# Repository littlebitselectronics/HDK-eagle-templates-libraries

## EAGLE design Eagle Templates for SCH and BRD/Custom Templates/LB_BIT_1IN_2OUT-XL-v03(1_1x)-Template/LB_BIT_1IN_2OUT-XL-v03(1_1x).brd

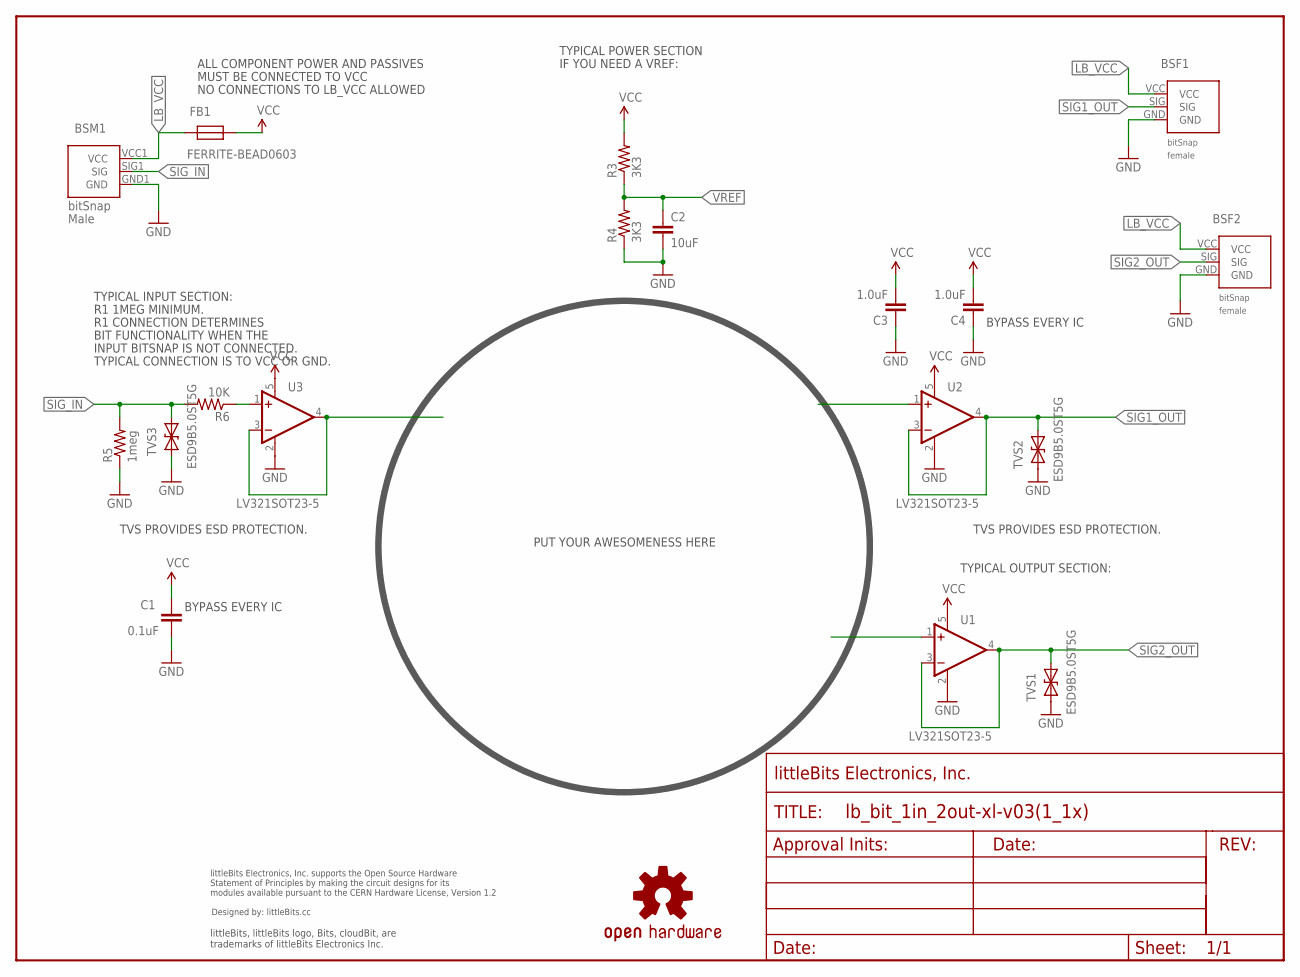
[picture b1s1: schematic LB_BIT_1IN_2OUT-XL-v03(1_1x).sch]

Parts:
BSF1, BSF2: BITSNAP_V03_FEMALE
BSM1: BITSNAP_V03_MALE
C1: 0.1uF; CAP-0603
C2: 10uF; CAP-0603
C3, C4: 1.0uF; CAP-0603
FB1: FERRITE-BEAD0603; R0603
FRAME1: FRAME-LETTER; FABDWG01-OHW
R3, R4: 3K3; RES-0603
R5: 1meg; RES-0603
R6: 10K; RES-0603
TVS1, TVS2, TVS3: ESD9B5.0ST5G; SOD-923
U1, U2, U3: LV321SOT23-5; SOT23-5
U$1: OSHW-LOGOL; OSHW-LOGO-L
U$2: OSHWCREDIT

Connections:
GND: BSF1.GND, BSF2.GND, BSM1.GND1 (GND), C1.2, C2.2, C3.1, C4.1, R4.1, R5.1, TVS1.1 (A), TVS2.1 (A), TVS3.1 (A), U1.2 (V-), U2.2 (V-), U3.2 (V-)
LB_VCC: BSF1.VCC, BSF2.VCC, BSM1.VCC1 (VCC), FB1.2
unnamed: U3.3 (-IN), U3.4 (OUT)
unnamed: R6.1, U3.1 (+IN)
SIG1_OUT: BSF1.SIG, TVS2.2 (C), U2.3 (-IN), U2.4 (OUT)
SIG2_OUT: BSF2.SIG, TVS1.2 (C), U1.3 (-IN), U1.4 (OUT)
SIG_IN: BSM1.SIG1 (SIG), R5.2, R6.2, TVS3.2 (C)
VCC: C1.1, C3.2, C4.2, FB1.1, R3.2, U1.5 (V+), U2.5 (V+), U3.5 (V+)
VREF: C2.1, R3.1, R4.2

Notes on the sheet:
R1 1MEG MINIMUM.
R1 CONNECTION DETERMINES
BIT FUNCTIONALITY WHEN THE
INPUT BITSNAP IS NOT CONNECTED.
TYPICAL CONNECTION IS TO VCC OR GND.
TVS PROVIDES ESD PROTECTION.
TYPICAL INPUT SECTION:
TYPICAL POWER SECTION
IF YOU NEED A VREF:
PUT YOUR AWESOMENESS HERE
BYPASS EVERY IC
TYPICAL OUTPUT SECTION:
NO CONNECTIONS TO LB_VCC ALLOWED
ALL COMPONENT POWER AND PASSIVES
MUST BE CONNECTED TO VCC

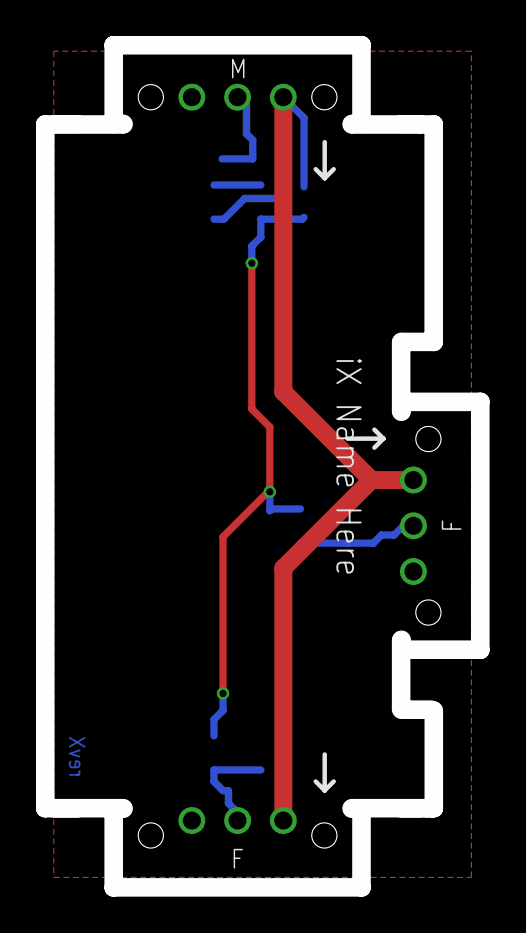
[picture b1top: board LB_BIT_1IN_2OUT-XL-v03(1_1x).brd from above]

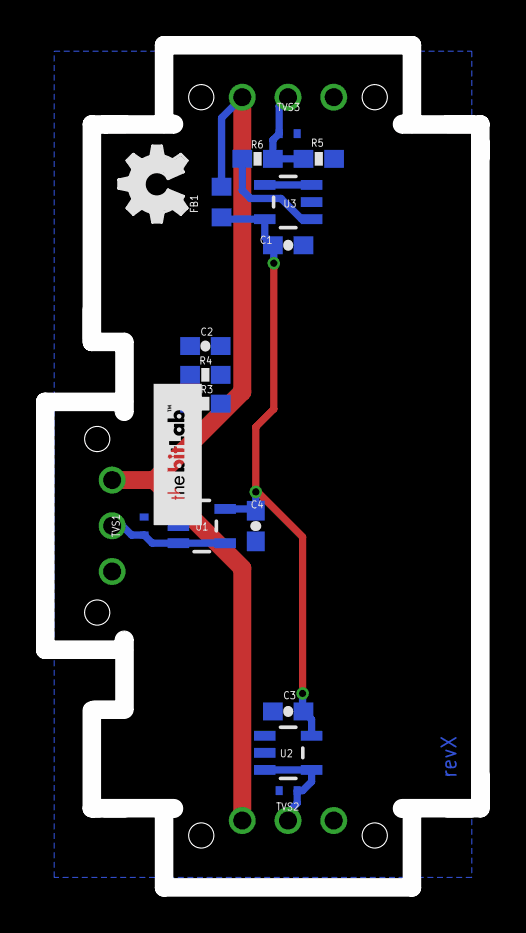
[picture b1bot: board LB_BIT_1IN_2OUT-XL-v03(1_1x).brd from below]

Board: 2 copper layers, 23.2 x 45.8 mm, 23 parts (15 on the bottom side), 9 nets.

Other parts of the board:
U$3: BITLAB-LOGO
U$8: OSHW_FILLX150_NOTEXT

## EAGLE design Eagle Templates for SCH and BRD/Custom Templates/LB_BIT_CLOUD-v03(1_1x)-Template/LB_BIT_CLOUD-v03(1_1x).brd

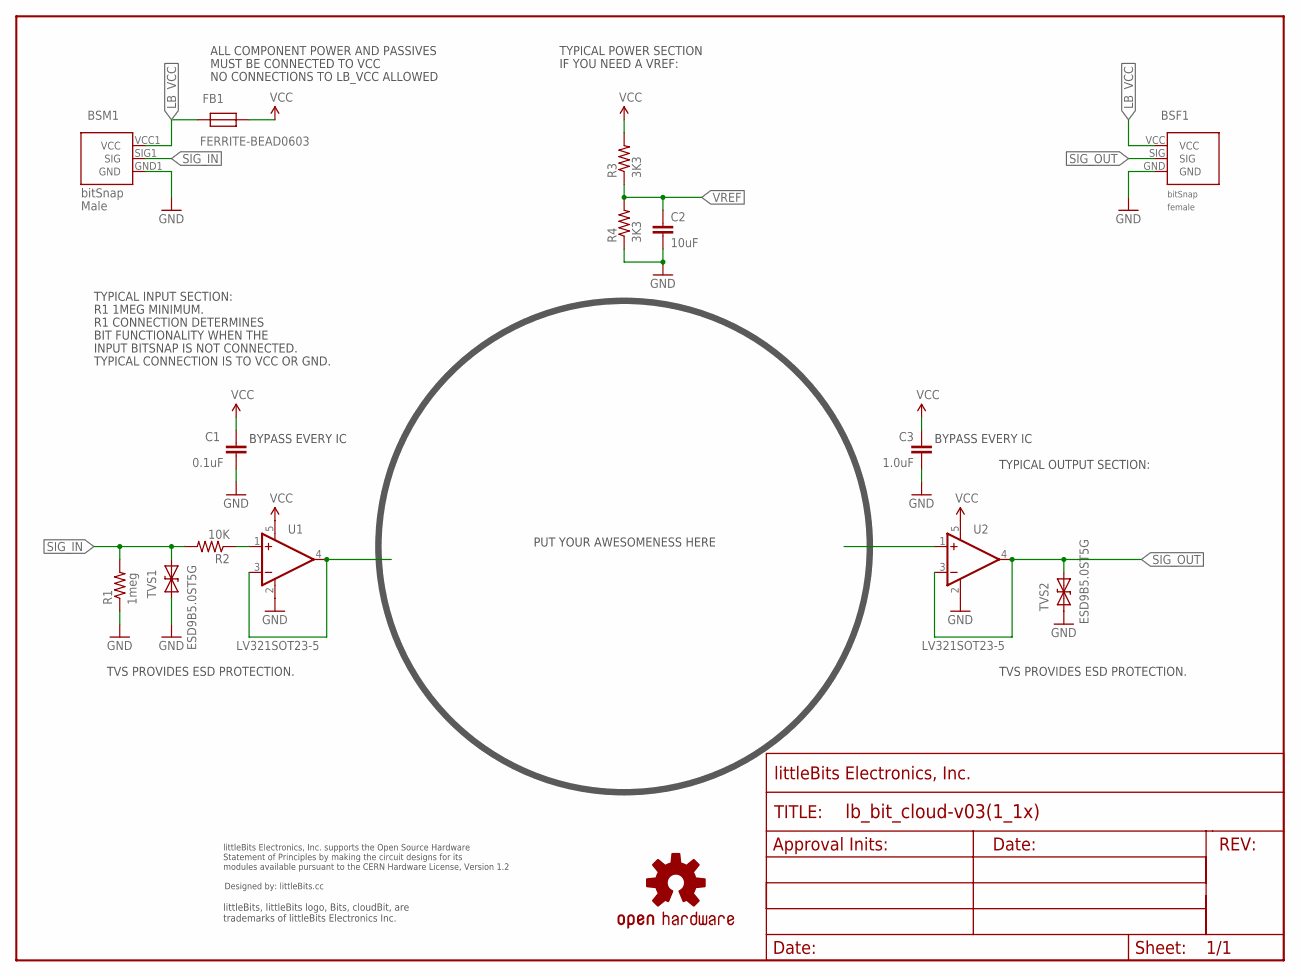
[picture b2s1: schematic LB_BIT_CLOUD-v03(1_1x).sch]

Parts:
BSF1: BITSNAP_V03_FEMALE
BSM1: BITSNAP_V03_MALE
C1: 0.1uF; CAP-0603
C2: 10uF; CAP-0603
C3: 1.0uF; CAP-0603
FB1: FERRITE-BEAD0603; R0603
FRAME1: FRAME-LETTER; FABDWG01-OHW
R1: 1meg; RES-0603
R2: 10K; RES-0603
R3, R4: 3K3; RES-0603
TVS1, TVS2: ESD9B5.0ST5G; SOD-923
U1, U2: LV321SOT23-5; SOT23-5
U$3: OSHWCREDIT
U$4: OSHW-LOGOL; OSHW-LOGO-L

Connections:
GND: BSF1.GND, BSM1.GND1 (GND), C1.2, C2.2, C3.1, R1.1, R4.1, TVS1.1 (A), TVS2.1 (A), U1.2 (V-), U2.2 (V-)
LB_VCC: BSF1.VCC, BSM1.VCC1 (VCC), FB1.2
unnamed: U1.3 (-IN), U1.4 (OUT)
unnamed: R2.1, U1.1 (+IN)
SIG_IN: BSM1.SIG1 (SIG), R1.2, R2.2, TVS1.2 (C)
SIG_OUT: BSF1.SIG, TVS2.2 (C), U2.3 (-IN), U2.4 (OUT)
VCC: C1.1, C3.2, FB1.1, R3.2, U1.5 (V+), U2.5 (V+)
VREF: C2.1, R3.1, R4.2

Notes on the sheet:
R1 1MEG MINIMUM.
R1 CONNECTION DETERMINES
BIT FUNCTIONALITY WHEN THE
INPUT BITSNAP IS NOT CONNECTED.
TYPICAL CONNECTION IS TO VCC OR GND.
TVS PROVIDES ESD PROTECTION.
TYPICAL INPUT SECTION:
TYPICAL POWER SECTION
IF YOU NEED A VREF:
TYPICAL OUTPUT SECTION:
PUT YOUR AWESOMENESS HERE
BYPASS EVERY IC
NO CONNECTIONS TO LB_VCC ALLOWED
ALL COMPONENT POWER AND PASSIVES
MUST BE CONNECTED TO VCC

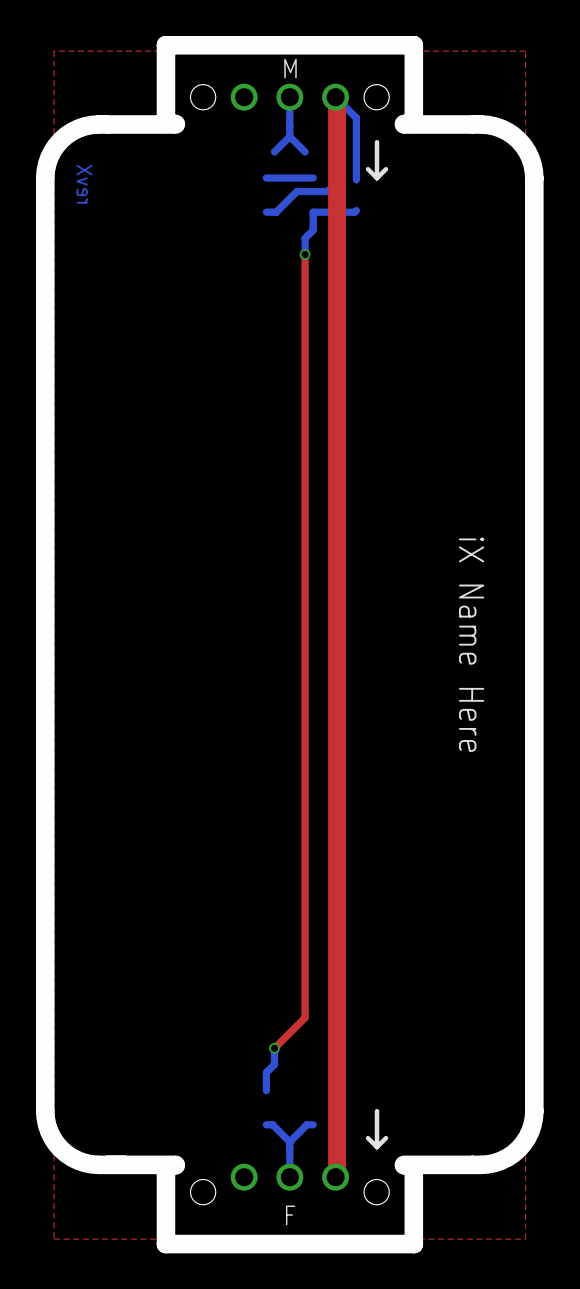
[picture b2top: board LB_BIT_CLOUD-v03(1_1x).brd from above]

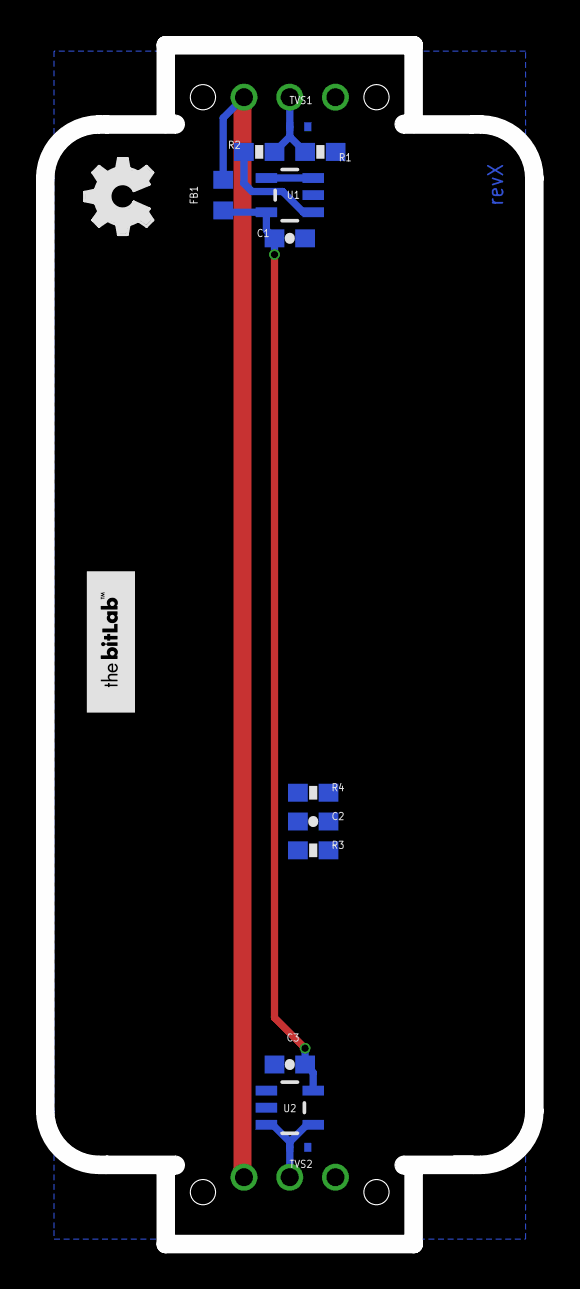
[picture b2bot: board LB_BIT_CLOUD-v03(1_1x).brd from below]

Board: 6 copper layers, 27.2 x 66.6 mm, 19 parts (13 on the bottom side), 8 nets.

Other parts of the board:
U$1: OSHW_FILLX150_NOTEXT
U$2: BITLAB-LOGO

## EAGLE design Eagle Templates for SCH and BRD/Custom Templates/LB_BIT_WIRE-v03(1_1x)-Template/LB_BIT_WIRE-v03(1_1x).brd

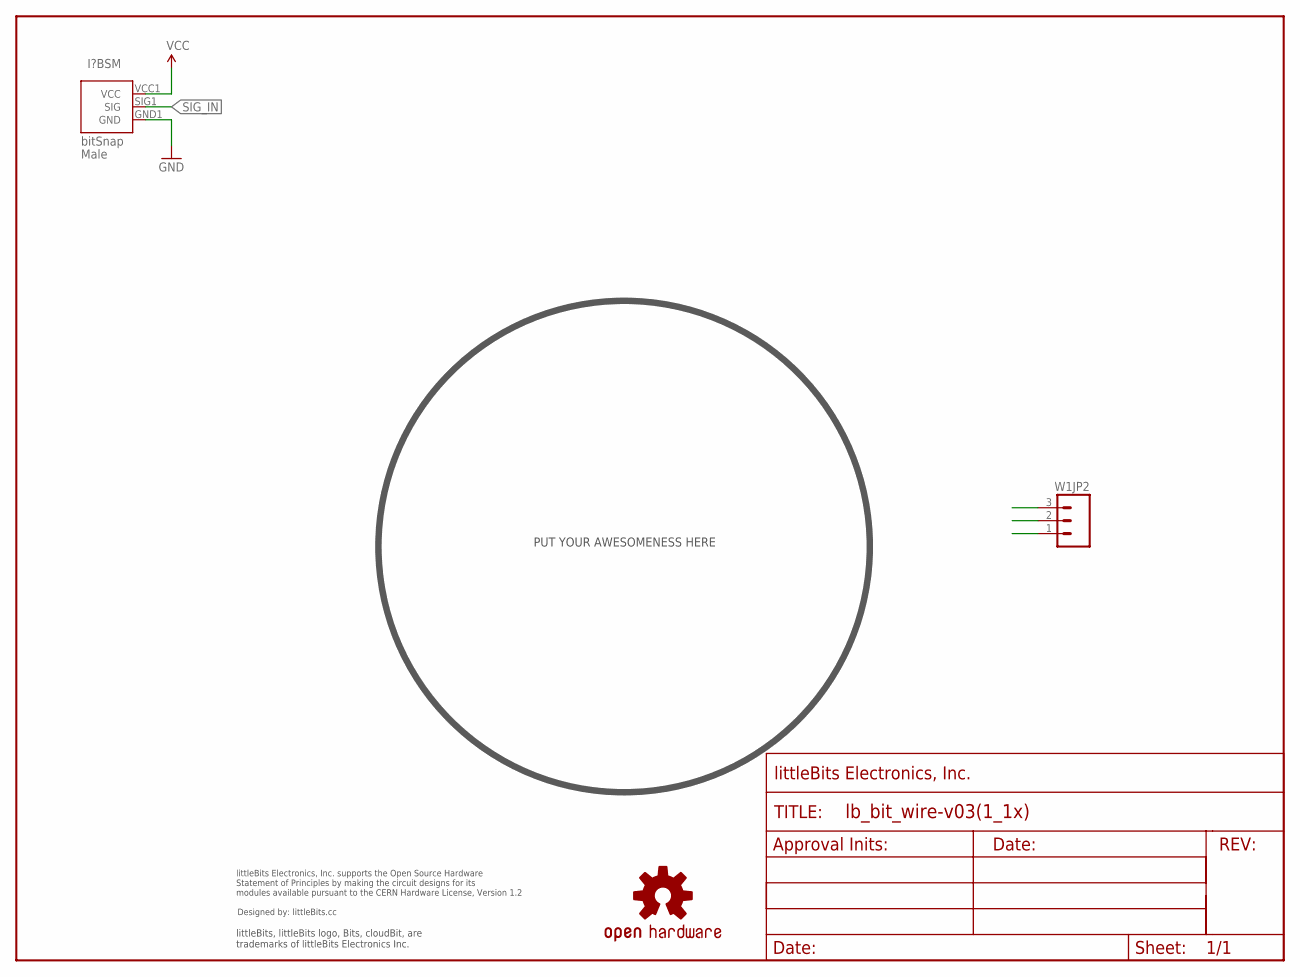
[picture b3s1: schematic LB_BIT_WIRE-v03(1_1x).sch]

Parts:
FRAME1: FRAME-LETTER; FABDWG01-OHW
I?BSM: BITSNAP_V03_MALE
U$2: OSHWCREDIT
U$5: OSHW-LOGOL; OSHW-LOGO-L
W1JP2: M03SMD; 1X03-1MM-RA

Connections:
GND: I?BSM.GND1 (GND), W1JP2.1
SIG: W1JP2.2
SIG_IN: I?BSM.SIG1 (SIG)
VCC: I?BSM.VCC1 (VCC), W1JP2.3

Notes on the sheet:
PUT YOUR AWESOMENESS HERE

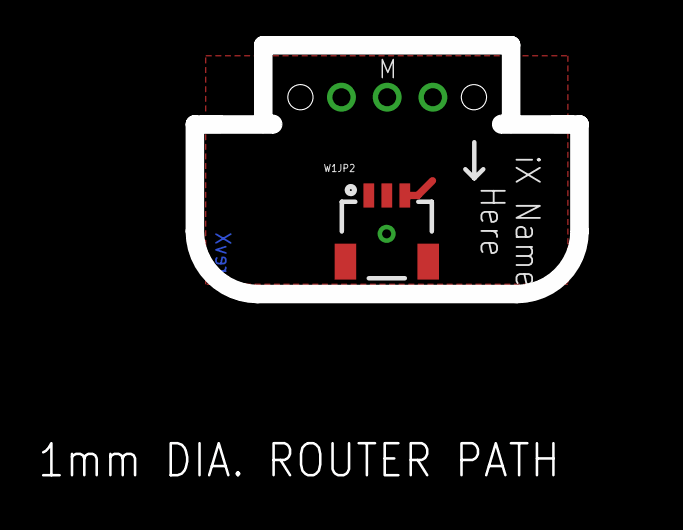
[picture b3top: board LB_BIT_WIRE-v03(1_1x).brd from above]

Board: 2 copper layers, 20.4 x 12.8 mm, 7 parts (0 on the bottom side), 2 nets.

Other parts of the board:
U$1: BITLAB-LOGO
U$4: OSHW_FILLX150_NOTEXT

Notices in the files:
parts and their libraries:
LITTLEBITS: modules available pursuant to the CERN Hardware License,
Version 1.2
LITTLEBITS: modules available pursuant to the CERN Hardware License, Version 1.2
SparkFun_NEW: Licensing: CC v3.0 Share-Alike You are welcome to use this library for commercial purposes.
